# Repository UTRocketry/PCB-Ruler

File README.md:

# PCB-Ruler
A simple PCB Ruler blinky

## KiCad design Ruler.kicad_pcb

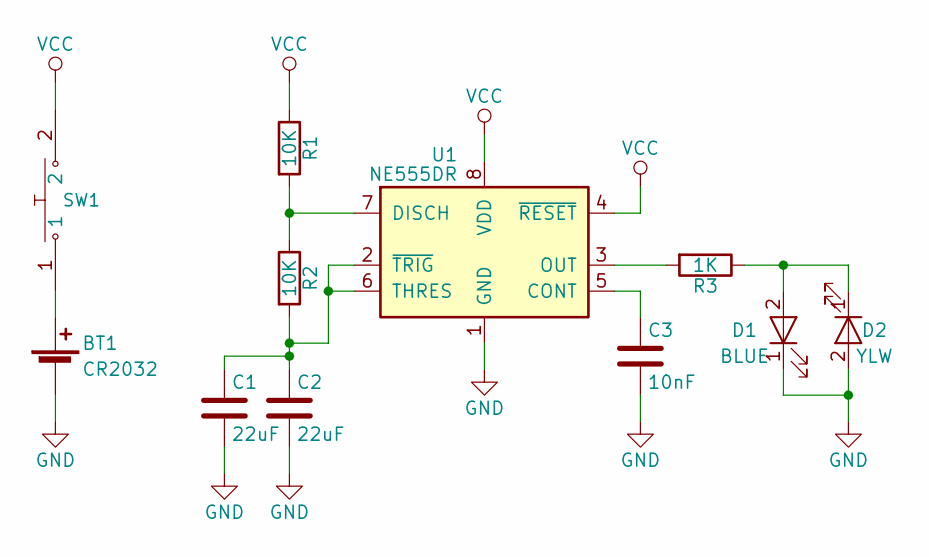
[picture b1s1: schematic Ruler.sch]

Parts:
BT1: CR2032; CR2032-BS-6-1; LCSC C70377
C1, C2: 22uF; C_0603; LCSC C59461
C3: 10nF; C_0805; LCSC C1710
D1: BLUE; LED_0805; LCSC C2293
D2: YLW; LED_0805; LCSC C2296
R1, R2: 10K; R_0805; LCSC C17414
R3: 1K; R_0805
SW1: Push_SW; SW_SPST_SKQG; LCSC C318889
U1: NE555DR; SOIC-8_3.9x4.9mm_Pitch1.27mm; LCSC C7593

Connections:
GND: BT1.2 (-), C1.2, C2.2, C3.2, D1.1 (K), D2.2 (A), U1.1 (GND)
unnamed: BT1.1 (+), SW1.1
unnamed: C1.1, C2.1, R2.2, U1.2 (~TRIG), U1.6 (THRES)
unnamed: C3.1, U1.5 (CONT)
unnamed: D1.2 (A), D2.1 (K), R3.1
unnamed: R1.2, R2.1, U1.7 (DISCH)
unnamed: R3.2, U1.3 (OUT)
VCC: R1.1, SW1.2, U1.4 (~RESET), U1.8 (VDD)

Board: 2 copper layers, 11 parts (0 on the bottom side), 8 nets, no tracks yet.

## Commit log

2020-07-13 init
